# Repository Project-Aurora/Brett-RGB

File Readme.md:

#Brett-RGB
A Plank-Compatible Keyboard with RomerG Switches and RGB LEDs

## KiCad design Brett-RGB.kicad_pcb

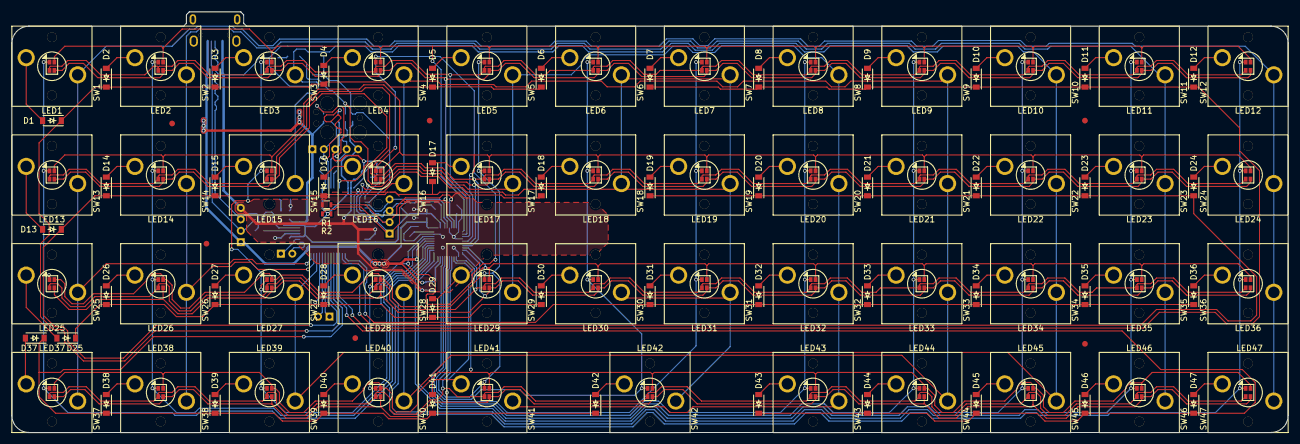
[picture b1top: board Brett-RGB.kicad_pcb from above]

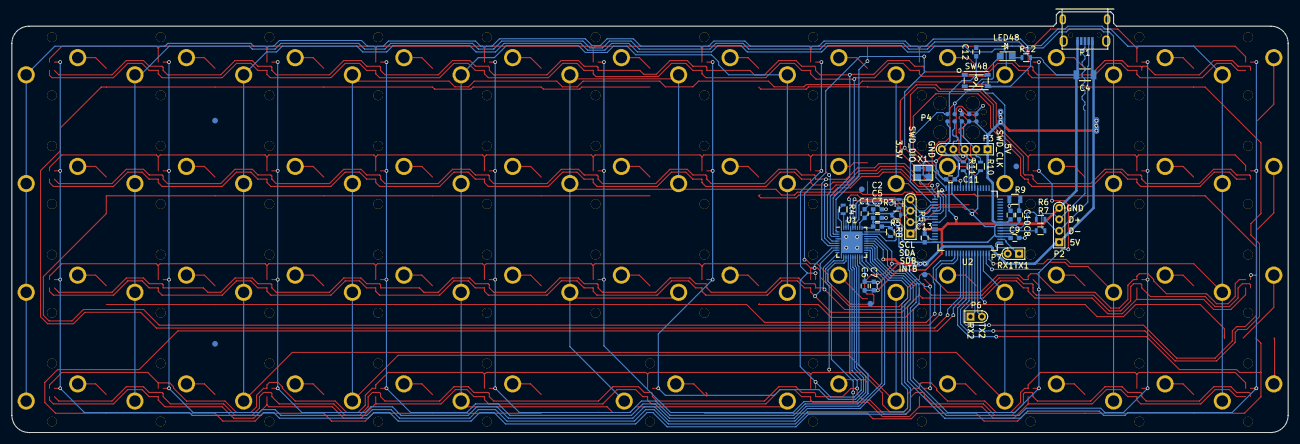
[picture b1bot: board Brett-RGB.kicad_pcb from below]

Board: 2 copper layers, 223.0 x 73.5 mm, 178 parts (35 on the bottom side), 114 nets.

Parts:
C1, C3, C6, C9, C11, C12, C13: 0.1uF; C_0603
C2, C5, C7: 1uF; C_0603
C4: 100uF; C_1206
C8, C10: 2.2uF; C_0603
D1, D2, D3, D4, D5, D6, D7, D8, D9, D10, D11, D12, D13, D14, D15, D16, D17, D18, D19, D20, D21, D22, D23, D24, D25, D26, D27, D28, D29, D30, D31, D32, D33, D34, D35, D36, D37, D38, D39, D40, D41, D42, D43, D44, D45, D46, D47: D_Small; SOD-123
LED1, LED2, LED3, LED4, LED5, LED6, LED7, LED8, LED9, LED10, LED11, LED12, LED13, LED14, LED15, LED16, LED17, LED18, LED19, LED20, LED21, LED22, LED23, LED24, LED25, LED26, LED27, LED28, LED29, LED30, LED31, LED32, LED33, LED34, LED35, LED36, LED37, LED38, LED39, LED40, LED41, LED42, LED43, LED44, LED45, LED46, LED47: Led_RGB_CA; RGB-0606
LED48: LED; LED_0805
P1: USB_OTG; Micro-USB_629105150521
P2, P5: CONN_01X04; Conn-4
P3: CONN_01X05; Conn-5
P4: FLASH_HDR; JLINK_NEEDLE
P6, P7: CONN_01X02; Conn-2
R1, R2, R4: 100k; R_0603
R3, R5: 4.7k; R_0603
R6, R7: 33; R_0603
R8: 20k; R_0603
R9: 5M; R_0805
R10, R11: 100; R_0603
R12: 1k; R_0603
SW1, SW2, SW3, SW4, SW5, SW6, SW7, SW8, SW9, SW10, SW11, SW12, SW13, SW14, SW15, SW16, SW17, SW18, SW19, SW20, SW21, SW22, SW23, SW24, SW25, SW26, SW27, SW28, SW29, SW30, SW31, SW32, SW33, SW34, SW35, SW36, SW37, SW38, SW39, SW40, SW41, SW42, SW43, SW44, SW45, SW46, SW47: SW_PUSH; RomerG
SW48: TAC_SWITCH; PTS810
U1: IS31FL3737; UQFN-40-1EP_5x5mm_Pitch0.4mm
U2: MK20DX256VLH7-RESCUE-RainbowFox; LQFP-64_10x10mm_Pitch0.5mm
X1: CRYSTAL_SMD; crystal_FA238-TSX3225

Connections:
+3V3: C1.1, C2.1, C8.1, C9.1, C11.1, C13.1, P3.5, P4.1, R2.1, R3.1, R5.1, U1.32, U2.3, U2.7, U2.21, U2.30, U2.48
+5V: C3.1, C4.1, C5.1, C6.1, C7.1, C10.1, P1.1, P2.1, P3.1, P4.5, U1.19, U1.26, U1.31, U2.8
/CS1: LED5.1, LED17.1, LED29.1, LED41.1, U1.15
/CS2: LED6.1, LED18.1, LED30.1, LED42.1, U1.16
/CS3: LED7.1, LED19.1, LED31.1, U1.17
/CS4: LED8.1, LED20.1, LED32.1, LED43.1, U1.18
/CS5: LED9.1, LED21.1, LED33.1, LED44.1, U1.20
/CS6: LED10.1, LED22.1, LED34.1, LED45.1, U1.21
/CS7: LED11.1, LED23.1, LED35.1, LED46.1, U1.22
/CS8: LED12.1, LED24.1, LED36.1, LED47.1, U1.23
/CS9: LED1.1, LED13.1, LED25.1, LED37.1, U1.24
/CS10: LED2.1, LED14.1, LED26.1, LED38.1, U1.25
/CS11: LED3.1, LED15.1, LED27.1, LED39.1, U1.27
/CS12: LED4.1, LED16.1, LED28.1, LED40.1, U1.28
/Col1: SW1.2, SW12.2, SW13.2, SW24.2, SW25.2, SW36.2, SW37.2, SW47.2, U2.64
/Col2: SW2.2, SW11.2, SW14.2, SW23.2, SW26.2, SW35.2, SW38.2, SW46.2, U2.63
/Col3: SW3.2, SW10.2, SW15.2, SW22.2, SW27.2, SW34.2, SW39.2, SW45.2, U2.62
/Col4: SW4.2, SW9.2, SW16.2, SW21.2, SW28.2, SW33.2, SW40.2, SW44.2, U2.41
/Col5: SW5.2, SW8.2, SW17.2, SW20.2, SW29.2, SW32.2, SW41.2, SW43.2, U2.37
/Col6: SW6.2, SW7.2, SW18.2, SW19.2, SW30.2, SW31.2, SW42.2, U2.38
/MCU/D+: R7.1, U2.5
/MCU/D-: R6.1, U2.6
/MCU/INTB: P5.1, R2.2, U1.37, U2.40
/MCU/MCU_RESET: C12.1, P4.10, SW48.2, U2.34
/MCU/PTA5: LED48.2, P4.9, U2.27
/MCU/RX0: P4.8, U2.23
/MCU/RX1: P7.2, U2.1
/MCU/RX2: P6.1, U2.59
/MCU/SCL: P5.4, R3.2, U1.35, U2.35
/MCU/SDA: P5.3, R5.2, U1.34, U2.36
/MCU/SDB: P5.2, R1.2, U1.38, U2.39
/MCU/SWD_CLK: P3.2, P4.4, R10.2
/MCU/SWD_DIO: P3.4, P4.2, R11.2
/MCU/TX0: P4.6, U2.24
/MCU/TX1: P7.1, U2.2
/MCU/TX2: P6.2, U2.60
/MCU/USB_D+: P1.3, P2.3, R7.2
/MCU/USB_D-: P1.2, P2.2, R6.2
/Row1: D1.1, D2.1, D3.1, D4.1, D5.1, D6.1, U2.57
/Row2: D13.1, D14.1, D15.1, D16.1, D17.1, D18.1, U2.58
/Row3: D25.1, D26.1, D27.1, D28.1, D29.1, D30.1, U2.61
/Row4: D37.1, D38.1, D39.1, D40.1, D41.1, D42.1, U2.56
/Row5: D7.1, D8.1, D9.1, D10.1, D11.1, D12.1, U2.54
/Row6: D19.1, D20.1, D21.1, D22.1, D23.1, D24.1, U2.53
/Row7: D31.1, D32.1, D33.1, D34.1, D35.1, D36.1, U2.52
/Row8: D43.1, D44.1, D45.1, D46.1, D47.1, U2.55
/SW1: LED1.2, LED2.2, LED3.2, LED4.2, LED5.2, LED6.2, LED7.2, LED8.2, LED9.2, LED10.2, LED11.2, LED12.2, U1.1
/SW2: LED1.3, LED2.3, LED3.3, LED4.3, LED5.3, LED6.3, LED7.3, LED8.3, LED9.3, LED10.3, LED11.3, LED12.3, U1.2
/SW3: LED1.4, LED2.4, LED3.4, LED4.4, LED5.4, LED6.4, LED7.4, LED8.4, LED9.4, LED10.4, LED11.4, LED12.4, U1.3
/SW4: LED13.2, LED14.2, LED15.2, LED16.2, LED17.2, LED18.2, LED19.2, LED20.2, LED21.2, LED22.2, LED23.2, LED24.2, U1.5
/SW5: LED13.3, LED14.3, LED15.3, LED16.3, LED17.3, LED18.3, LED19.3, LED20.3, LED21.3, LED22.3, LED23.3, LED24.3, U1.6
/SW6: LED13.4, LED14.4, LED15.4, LED16.4, LED17.4, LED18.4, LED19.4, LED20.4, LED21.4, LED22.4, LED23.4, LED24.4, U1.7
/SW7: LED25.2, LED26.2, LED27.2, LED28.2, LED29.2, LED30.2, LED31.2, LED32.2, LED33.2, LED34.2, LED35.2, LED36.2, U1.8
/SW8: LED25.3, LED26.3, LED27.3, LED28.3, LED29.3, LED30.3, LED31.3, LED32.3, LED33.3, LED34.3, LED35.3, LED36.3, U1.9
/SW9: LED25.4, LED26.4, LED27.4, LED28.4, LED29.4, LED30.4, LED31.4, LED32.4, LED33.4, LED34.4, LED35.4, LED36.4, U1.10
/SW10: LED37.2, LED38.2, LED39.2, LED40.2, LED41.2, LED42.2, LED43.2, LED44.2, LED45.2, LED46.2, LED47.2, U1.12
/SW11: LED37.3, LED38.3, LED39.3, LED40.3, LED41.3, LED42.3, LED43.3, LED44.3, LED45.3, LED46.3, LED47.3, U1.13
/SW12: LED37.4, LED38.4, LED39.4, LED40.4, LED41.4, LED42.4, LED43.4, LED44.4, LED45.4, LED46.4, LED47.4, U1.14
GND: C1.2, C2.2, C3.2, C4.2, C5.2, C6.2, C7.2, C9.2, C10.2, C11.2, C12.2, C13.2, P1.5, P2.4, P3.3, P4.3, R1.1, R4.1, R8.2, R9.2, R12.2, SW48.4, U1.4, U1.11, U1.29, U1.36, U1.40, U1.41, U2.4, U2.31, U2.47, X1.3
unnamed: C8.2, R9.1
unnamed: D1.2, SW1.1
unnamed: D2.2, SW2.1
unnamed: D3.2, SW3.1
unnamed: D4.2, SW4.1
unnamed: D5.2, SW5.1
unnamed: D6.2, SW6.1
unnamed: D7.2, SW7.1
unnamed: D8.2, SW8.1
unnamed: D9.2, SW9.1
unnamed: D10.2, SW10.1
unnamed: D11.2, SW11.1
unnamed: D12.2, SW12.1
unnamed: D13.2, SW13.1
unnamed: D14.2, SW14.1
unnamed: D15.2, SW15.1
unnamed: D16.2, SW16.1
unnamed: D17.2, SW17.1
unnamed: D18.2, SW18.1
unnamed: D19.2, SW19.1
unnamed: D20.2, SW20.1
unnamed: D21.2, SW21.1
unnamed: D22.2, SW22.1
unnamed: D23.2, SW23.1
unnamed: D24.2, SW24.1
unnamed: D25.2, SW25.1
unnamed: D26.2, SW26.1
unnamed: D27.2, SW27.1
unnamed: D28.2, SW28.1
unnamed: D29.2, SW29.1
unnamed: D30.2, SW30.1
unnamed: D31.2, SW31.1
unnamed: D32.2, SW32.1
unnamed: D33.2, SW33.1
unnamed: D34.2, SW34.1
unnamed: D35.2, SW35.1
unnamed: D36.2, SW36.1
unnamed: D37.2, SW37.1
unnamed: D38.2, SW38.1
unnamed: D39.2, SW39.1
unnamed: D40.2, SW40.1
unnamed: D41.2, SW41.1
unnamed: D42.2, SW42.1
unnamed: D43.2, SW43.1
unnamed: D44.2, SW44.1
unnamed: D45.2, SW45.1
unnamed: D46.2, SW46.1
unnamed: D47.2, SW47.1
unnamed: LED48.1, R12.1
unnamed: R4.2, U1.39
unnamed: R8.1, U1.30
unnamed: R10.1, U2.22
unnamed: R11.1, U2.25
unnamed: U2.32, X1.1
unnamed: U2.33, X1.2

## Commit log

2016-06-01 :space_invader: Added .gitattributes & .gitignore files
2016-06-01 Remove unnecessary net file
2016-07-31 Reworked the Board
2016-08-02 Added Fiducials and Pintout Description
2017-01-16 Performed the changes from https://github.com/Project-Aurora/RainbowFox/commit/d956c5c3914152606eb0eeb9caeb00dc6e36fd84
    Added Resistor to ground for firmware-LED
    Connect VBAT to 3.3V
2017-01-29 Added Pinout for 3.3V
2017-02-21 Fixed MCU name in Schematic
